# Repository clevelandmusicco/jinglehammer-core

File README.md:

# Jinglehammer Core - Programmable MIDI Controller

The Jinglehammer Core is a 4 footswitch x 8 bank MIDI controller initially
designed for use with guitar effect pedals, but it can be used to control
anything that understands MIDI messages. Press a footswitch and it sends a
configurable bundle of Program Change and Control Change messages, with each
message free to target its own channel. Configuration lives in onboard flash
and survives power cycles; you edit it from a browser over USB, so there's no
separate app to install.

This repo holds the whole project: `software/` (RP2350 firmware plus the
browser-based config editor), `hardware/` (enclosure CAD and PCB design), and
`docs/` (design notes not tied to a single build artifact).

- Firmware is C + CMake with a VSCode workspace file provided
- Configuration webapp is simple HTML + Javascript with Python used for
  "building"
- PCB sources are in KiCad format and the Gerbers are tested at JLCPCB
- The enclosure source is provided in FreeCAD format, with STEP and 3MF files
  for use in your slicer of choice
  
> [!NOTE]
> Pictures of the hardware and the webapp coming soon.

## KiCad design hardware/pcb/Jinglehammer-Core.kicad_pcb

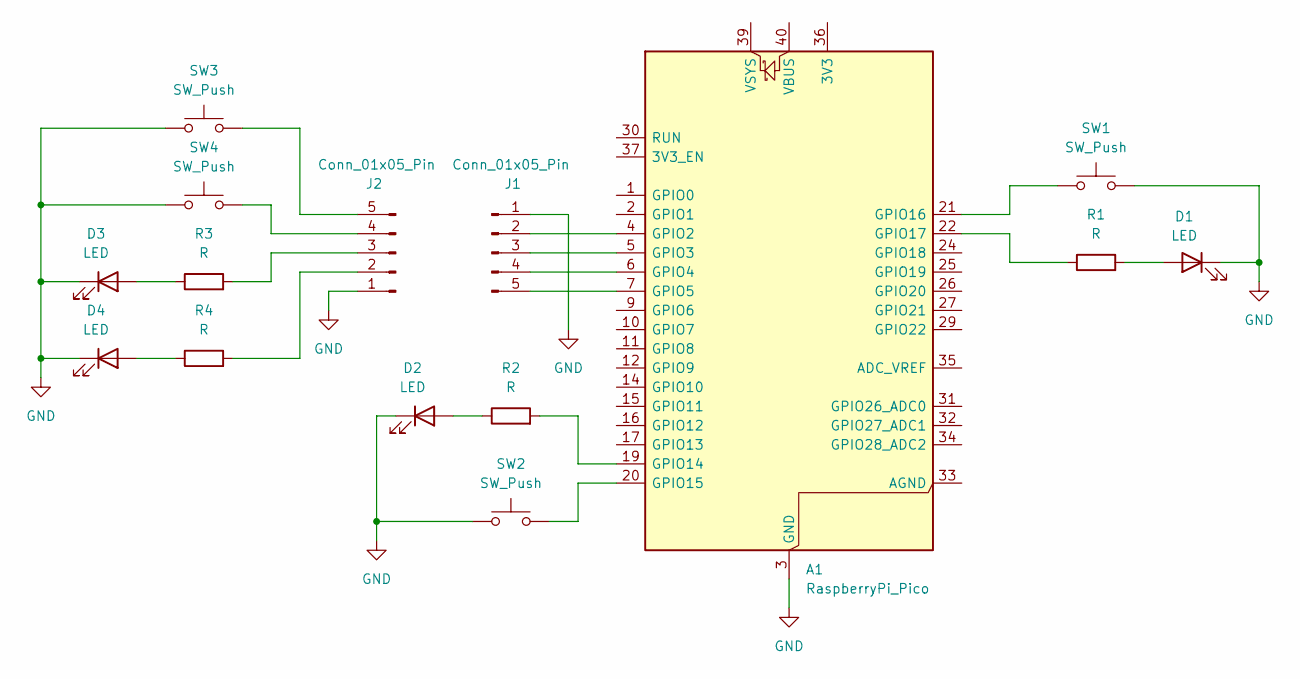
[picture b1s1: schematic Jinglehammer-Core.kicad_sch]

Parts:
A1: RaspberryPi_Pico; RaspberryPi_Pico_Common_Unspecified
D1, D2, D3, D4: LED; LED_D5.0mm
J1, J2: Conn_01x05_Pin; PinHeader_1x05_P2.54mm_Vertical
R1, R2, R3, R4: R; R_Axial_DIN0207_L6.3mm_D2.5mm_P7.62mm_Horizontal
SW1, SW2, SW3, SW4: SW_Push; Switch_Footswitch_PBS-24B-2_DirectMount

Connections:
GND: A1.3 (GND), A1.8 (GND), A1.13 (GND), A1.18 (GND), A1.23 (GND), A1.28 (GND), A1.38 (GND), D1.1 (K), D2.1 (K), D3.1 (K), D4.1 (K), J1.1, J2.1, SW1.1, SW2.1, SW3.1, SW4.1
unnamed: A1.4 (GPIO2), J1.2
unnamed: A1.5 (GPIO3), J1.3
unnamed: A1.6 (GPIO4), J1.4
unnamed: A1.7 (GPIO5), J1.5
unnamed: A1.19 (GPIO14), R2.2
unnamed: A1.20 (GPIO15), SW2.2
unnamed: A1.21 (GPIO16), SW1.2
unnamed: A1.22 (GPIO17), R1.1
unnamed: D1.2 (A), R1.2
unnamed: D2.2 (A), R2.1
unnamed: D3.2 (A), R3.1
unnamed: D4.2 (A), R4.1
unnamed: J2.2, R4.2
unnamed: J2.3, R3.2
unnamed: J2.4, SW4.2
unnamed: J2.5, SW3.2

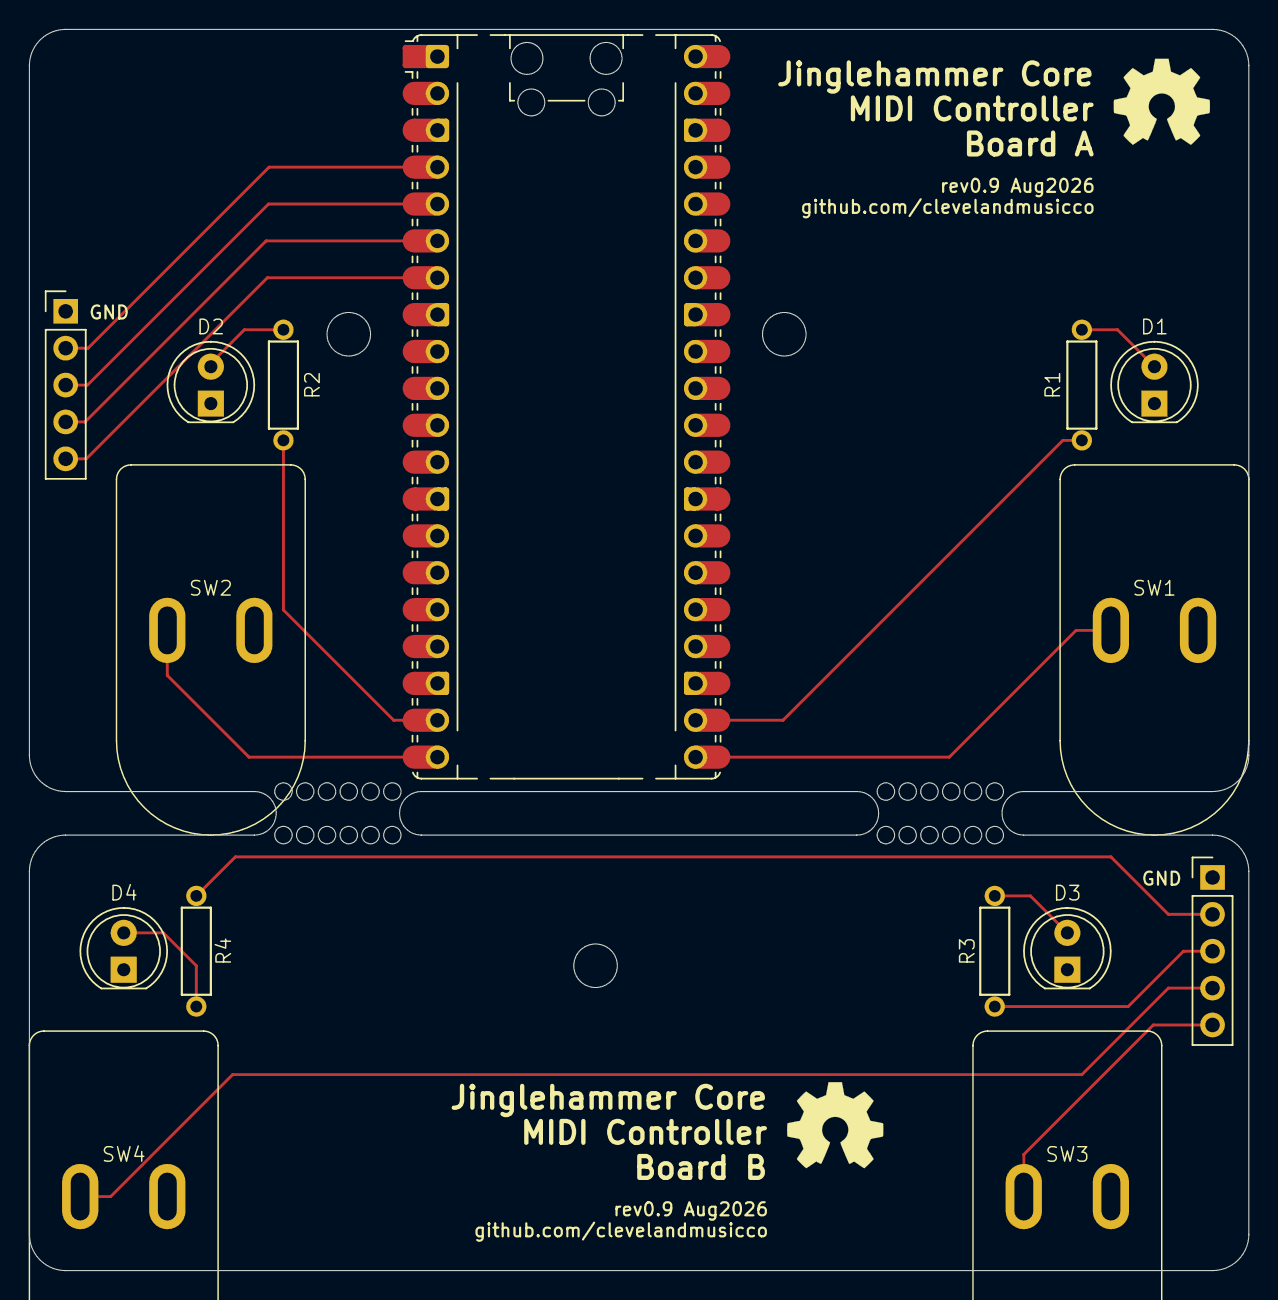
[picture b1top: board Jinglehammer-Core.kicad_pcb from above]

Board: 2 copper layers, 84.0 x 85.5 mm, 15 parts (0 on the bottom side), 17 nets.
